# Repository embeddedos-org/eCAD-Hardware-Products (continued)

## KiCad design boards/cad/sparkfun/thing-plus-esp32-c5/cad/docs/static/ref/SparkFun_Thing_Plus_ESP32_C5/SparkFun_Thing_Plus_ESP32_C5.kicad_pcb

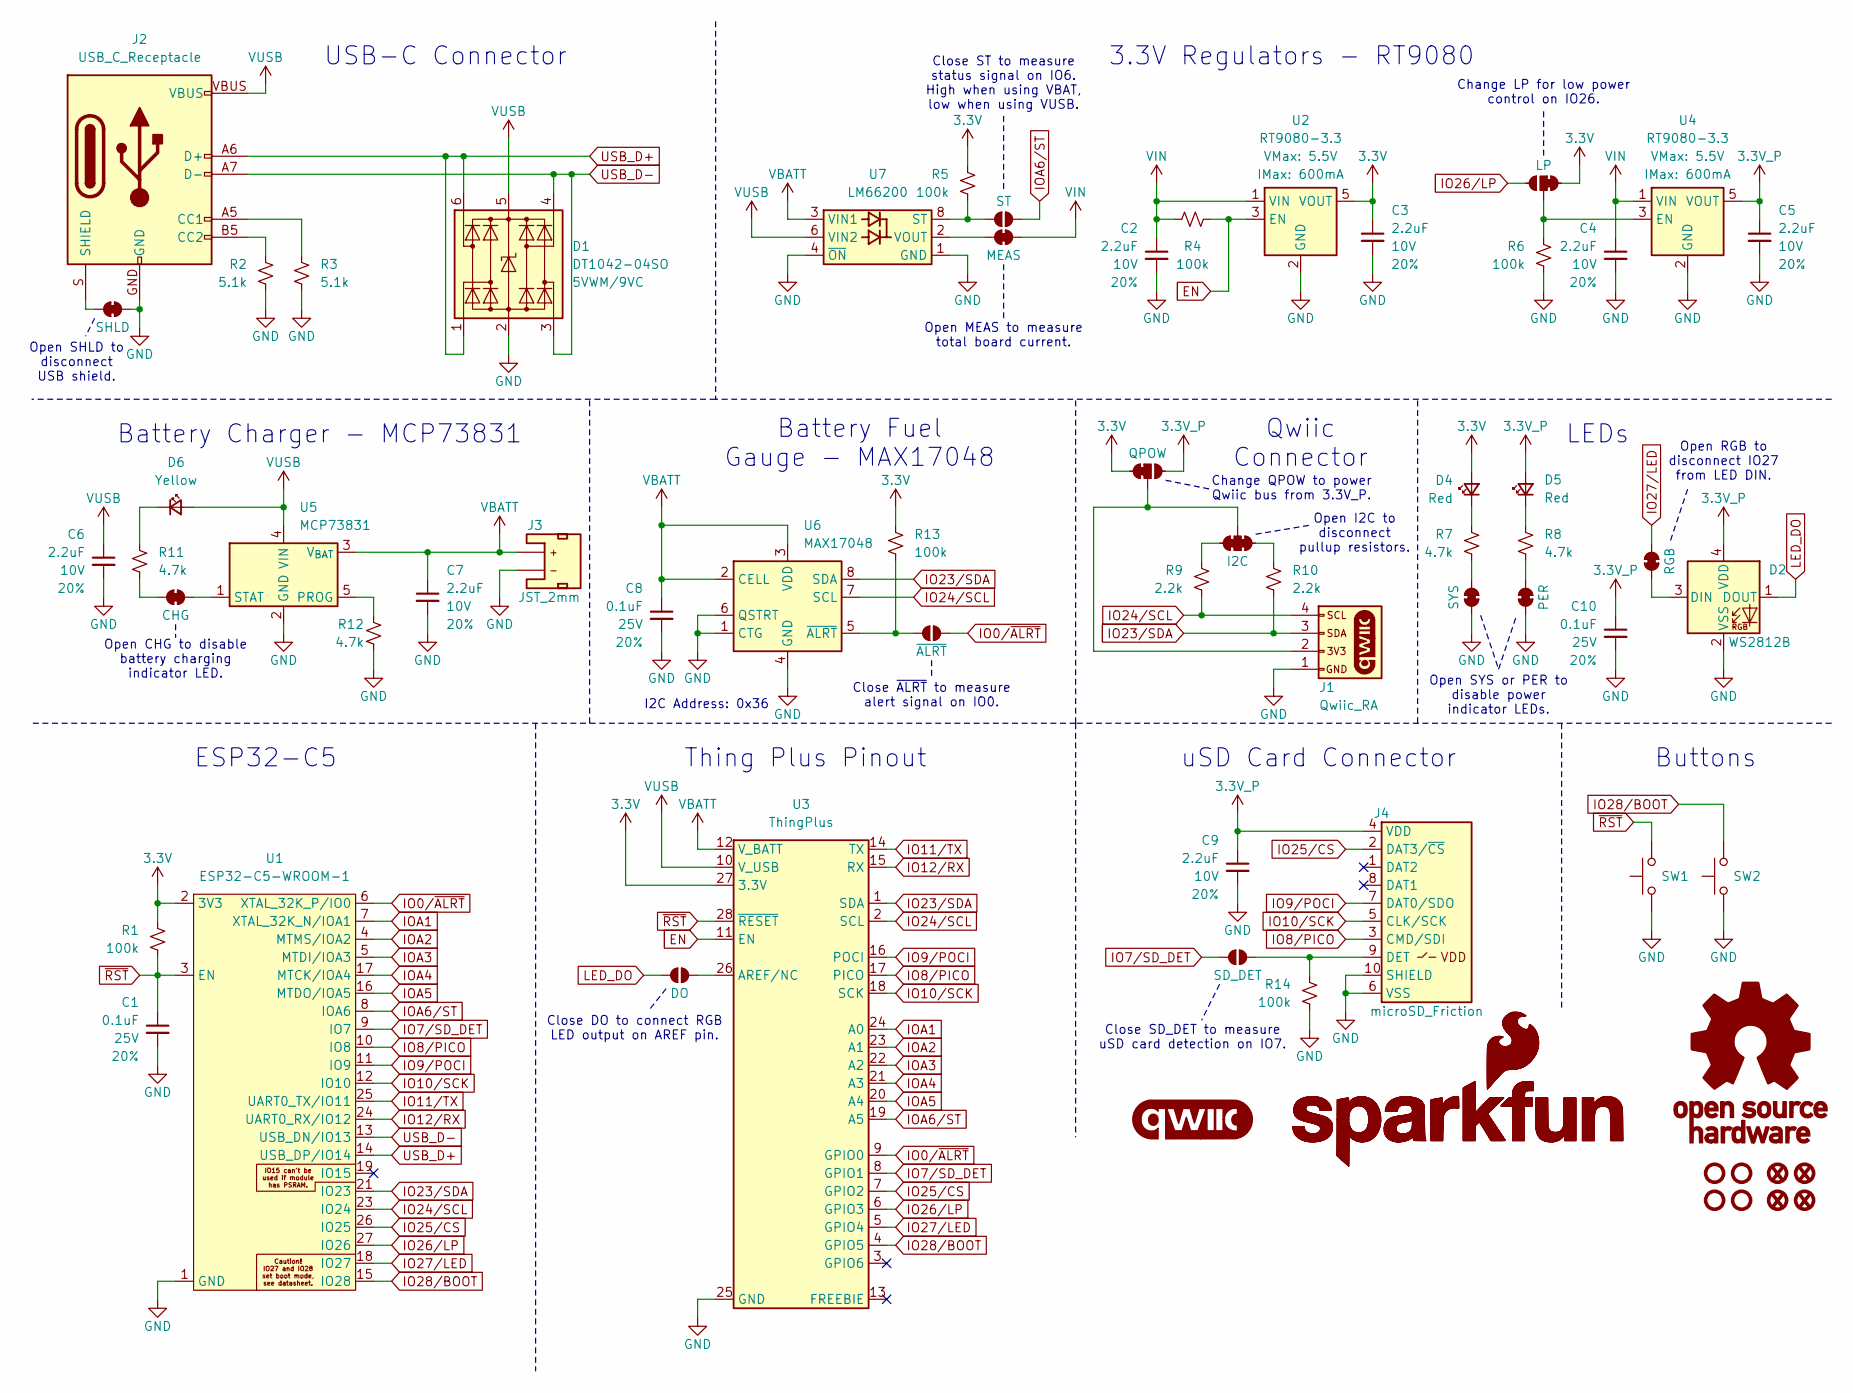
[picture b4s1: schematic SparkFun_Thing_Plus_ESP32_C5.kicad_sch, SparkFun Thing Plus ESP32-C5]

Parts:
C1, C8, C10: 0.1uF; C_0603_1608Metric; Voltage 25V; Tolerance 20%
C2, C3, C4, C5, C6, C7, C9: 2.2uF; C_0603_1608Metric; Voltage 10V; Tolerance 20%
D1: DT1042-04SO; SOT23-6; Rating 5VWM/9VC
D2: WS2812B; WS2812_2020
D4, D5: Red; LED_0603_1608Metric_Red
D6: Yellow; LED_0603_1608Metric_Yellow
FID1, FID2, FID3, FID4: Fiducial_0.5mm; Fiducial_0.5mm_Mask1mm
G1: SparkFun_Logo; SparkFun_Logo_8mm
G2: SparkFun_Logo
G3: OSHW_Logo; Creative_Commons_License
G4: qwiic_Logo
J1: Qwiic_RA; JST_1x04_P1.0mm_Horizontal_SMD
J2: USB_C_Receptacle; USB-C_16
J3: JST_2mm; JST_1x02_P2.0mm_Horizontal_SMD
J4: microSD_Friction; microSD_Friction_Fit_Common
JP1: SHLD; Jumper_2_NC_Trace
JP2: MEAS; Jumper_2_PTH_SMD_Combo-NC
JP3: LP; Jumper_3_NC-1_Trace
JP4: SYS; Jumper_2_NC_Trace
JP5: PER; Jumper_2_NC_Trace
JP6: I2C; Jumper_3_NC-2_Trace
JP7: QPOW; Jumper_3_NC-1_Trace
JP8: CHG; Jumper_2_NC_Trace
JP9: ~{ALRT}; Jumper_2_NO
JP10: SD_DET; Jumper_2_NO
JP11: DO; Jumper_2_NO
JP12: RGB; Jumper_2_NC_Trace
JP13: ST; Jumper_2_NO
R1, R4, R5, R6, R13, R14: 100k; R_0603_1608Metric
R2, R3: 5.1k; R_0603_1608Metric
R7, R8, R11, R12: 4.7k; R_0603_1608Metric
R9, R10: 2.2k; R_0603_1608Metric
ST1, ST2, ST3, ST4: Stand_off; Standoff
SW1, SW2: SMD_4.6x2.8mm_h2.5mm; Push_SMD_4.6x2.8mm_h2.5mm
U1: ESP32-C5-WROOM-1; ESP32-C5-WROOM-1-NARROW
U2, U4: RT9080-3.3; SOT23-5
U3: ThingPlus; ThingPlus_With_Connectors
U5: MCP73831; SOT23-5
U6: MAX17048; DFN-8_2x2mm_P0.5mm_EP1.2x0.8mm
U7: LM66200; SOT-583-8

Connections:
3.3V: C3.1, D4.2 (A), JP3.1 (A), JP7.1 (A), R1.2, R5.2, R13.2, U1.2 (3V3), U2.5 (VOUT), U3.27 (3.3V)
3.3V_P: C5.1, C9.1, C10.1, D2.4 (VDD), D5.2 (A), J4.4 (VDD), JP7.3 (C), U4.5 (VOUT)
EN: R4.2, U2.3 (EN), U3.11 (EN)
GND: C1.2, C2.2, C3.2, C4.2, C5.2, C6.2, C7.2, C8.2, C9.2, C10.2, D1.2 (GND), D2.2 (VSS), J1.1, J2.GND, J3.1 (-), J4.6 (VSS), J4.10 (SHIELD), JP1.2 (B), JP4.1 (A), JP5.1 (A), R2.1, R3.1, R6.1, R12.1, R14.1, SW1.1, SW2.1, U1.1 (GND), U1.28 (GND), U1.EPAD (GND), U2.2 (GND), U3.25 (GND), U4.2 (GND), U5.2 (GND), U6.1 (CTG), U6.4 (GND), U6.6 (QSTRT), U6.9 (GND), U7.1 (GND), U7.4 (~ON), U7.5 (GND)
IO0/~ALRT: JP9.2 (B), U1.6 (XTAL_32K_P/IO0), U3.9 (GPIO0)
IO7/SD_DET: JP10.1 (A), U1.9 (IO7), U3.8 (GPIO1)
IO8/PICO: J4.3 (CMD/SDI), U1.10 (IO8), U3.17 (PICO)
IO9/POCI: J4.7 (DAT0/SDO), U1.11 (IO9), U3.16 (POCI)
IO10/SCK: J4.5 (CLK/SCK), U1.12 (IO10), U3.18 (SCK)
IO11/TX: U1.25 (UART0_TX/IO11), U3.14 (TX)
IO12/RX: U1.24 (UART0_RX/IO12), U3.15 (RX)
IO23/SDA: J1.3, R10.1, U1.21 (IO23), U3.1 (SDA), U6.8 (SDA)
IO24/SCL: J1.4, R9.1, U1.23 (IO24), U3.2 (SCL), U6.7 (SCL)
IO25/CS: J4.2 (DAT3/~CS), U1.26 (IO25), U3.7 (GPIO2)
IO26/LP: JP3.3 (C), U1.27 (IO26), U3.6 (GPIO3)
IO27/LED: JP12.2 (B), U1.18 (IO27), U3.5 (GPIO4)
IO28/BOOT: SW2.2, U1.15 (IO28), U3.4 (GPIO5)
IOA1: U1.7 (XTAL_32K_N/IOA1), U3.24 (A0)
IOA2: U1.4 (MTMS/IOA2), U3.23 (A1)
IOA3: U1.5 (MTDI/IOA3), U3.22 (A2)
IOA4: U1.17 (MTCK/IOA4), U3.21 (A3)
IOA5: U1.16 (MTDO/IOA5), U3.20 (A4)
IOA6/ST: JP13.2 (B), U1.8 (IOA6), U3.19 (A5)
LED_DO: D2.1 (DOUT), JP11.1 (A)
unnamed: D2.3 (DIN), JP12.1 (A)
unnamed: D4.1 (K), R7.2
unnamed: D5.1 (K), R8.2
unnamed: D6.1 (K), R11.2
unnamed: J1.2, JP6.2 (B), JP7.2 (B)
unnamed: J2.A5 (CC1), R3.2
unnamed: J2.B5 (CC2), R2.2
unnamed: J2.S (SHIELD), JP1.1 (A)
unnamed: J4.9 (DET), JP10.2 (B), R14.2
unnamed: JP2.1 (A), U7.2 (VOUT), U7.7 (VOUT)
unnamed: JP3.2 (B), R6.2, U4.3 (EN)
unnamed: JP4.2 (B), R7.1
unnamed: JP5.2 (B), R8.1
unnamed: JP6.1 (A), R10.2
unnamed: JP6.3 (C), R9.2
unnamed: JP8.1 (A), R11.1
unnamed: JP8.2 (B), U5.1 (STAT)
unnamed: JP9.1 (A), R13.1, U6.5 (~ALRT)
unnamed: JP11.2 (B), U3.26 (AREF/NC)
unnamed: JP13.1 (A), R5.1, U7.8 (ST)
unnamed: R12.2, U5.5 (PROG)
USB_D+: D1.1 (I/O1), D1.6 (I/O4), J2.A6 (D+), J2.B6 (D+), U1.14 (USB_DP/IO14)
USB_D-: D1.3 (I/O2), D1.4 (I/O3), J2.A7 (D-), J2.B7 (D-), U1.13 (USB_DN/IO13)
VBATT: C7.1, C8.1, J3.2 (+), U3.12 (V_BATT), U5.3 (V_{BAT}), U6.2 (CELL), U6.3 (VDD), U7.3 (VIN1)
VIN: C2.1, C4.1, JP2.2 (B), R4.1, U2.1 (VIN), U4.1 (VIN)
VUSB: C6.1, D1.5 (VCC), D6.2 (A), J2.VBUS, U3.10 (V_USB), U5.4 (VIN), U7.6 (VIN2)
~RST: C1.1, R1.1, SW1.2, U1.3 (EN), U3.28 (~RESET)

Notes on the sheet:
uSD Card Connector
Open MEAS to measure total board current.
Close SD_DET to measure uSD card detection on IO7.
Open RGB to disconnect IO27 from LED DIN.
3.3V Regulators - RT9080
Close DO to connect RGB LED output on AREF pin.
Qwiic Connector
Thing Plus Pinout
Battery Fuel Gauge - MAX17048
Open SYS or PER to disable power indicator LEDs.
ESP32-C5
Change LP for low power control on IO26.
Close ~{ALRT} to measure alert signal on IO0.
LEDs
Open SHLD to disconnect USB shield.
I2C Address: 0x36
Open CHG to disable battery charging indicator LED.
Battery Charger - MCP73831
Close ST to measure status signal on IO6. High when using VBAT, low when using VUSB.
Open I2C to disconnect pullup resistors.
Change QPOW to power Qwiic bus from 3.3V_P.
USB-C Connector
Buttons

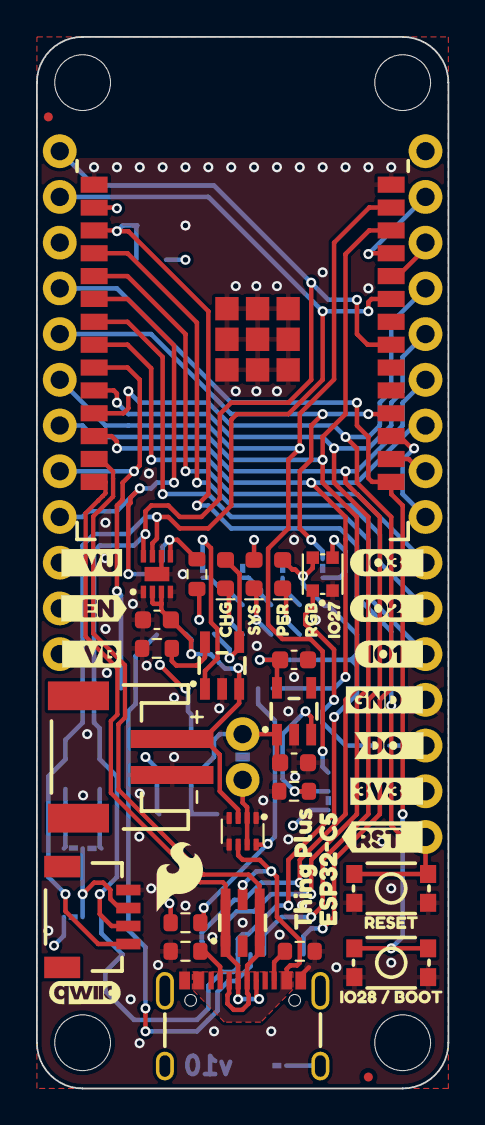
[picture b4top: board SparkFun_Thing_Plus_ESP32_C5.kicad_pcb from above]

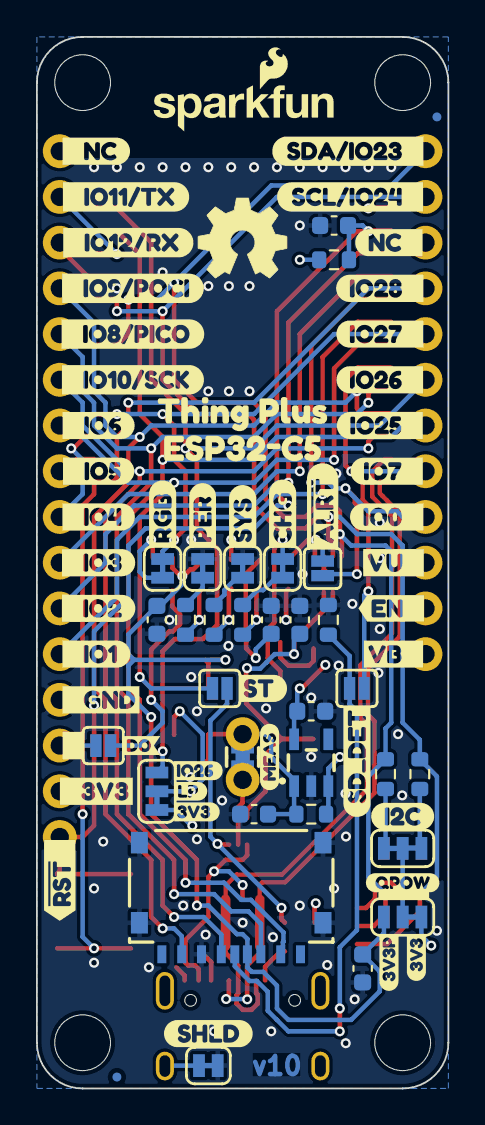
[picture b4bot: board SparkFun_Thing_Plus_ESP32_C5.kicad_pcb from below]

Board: 4 copper layers, 22.9 x 58.4 mm, 130 parts (79 on the bottom side), 51 nets.

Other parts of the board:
Ref**: Val**; OSHW_Logo_5mm
kibuzzard-695FE9C9: G***; kibuzzard-695FE9C9
kibuzzard-695FE9D0: G***; kibuzzard-695FE9D0
kibuzzard-695FE9E2: G***; kibuzzard-695FE9E2
kibuzzard-695FE9F2: G***; kibuzzard-695FE9F2
kibuzzard-695FEA02: G***; kibuzzard-695FEA02
kibuzzard-695FEA05: G***; kibuzzard-695FEA05
kibuzzard-695FEA11: G***; kibuzzard-695FEA11
kibuzzard-695FEF26: G***; kibuzzard-695FEF26
kibuzzard-695FEF91: G***; kibuzzard-695FEF91
kibuzzard-695FF00A: G***; kibuzzard-695FF00A
kibuzzard-695FF0A1: G***; kibuzzard-695FF0A1
kibuzzard-695FF0A5: G***; kibuzzard-695FF0A5
kibuzzard-695FF0AF: G***; kibuzzard-695FF0AF
kibuzzard-695FF0B3: G***; kibuzzard-695FF0B3
kibuzzard-695FF0B8: G***; kibuzzard-695FF0B8
kibuzzard-695FF0BC: G***; kibuzzard-695FF0BC
kibuzzard-695FF0C2: G***; kibuzzard-695FF0C2
kibuzzard-695FF0C6: G***; kibuzzard-695FF0C6
kibuzzard-695FF03A: G***; kibuzzard-695FF03A
kibuzzard-695FF06A: G***; kibuzzard-695FF06A
kibuzzard-695FF07F: G***; kibuzzard-695FF07F
kibuzzard-695FF09A: G***; kibuzzard-695FF09A
kibuzzard-695FF023: G***; kibuzzard-695FF023
kibuzzard-695FF029: G***; kibuzzard-695FF029
kibuzzard-695FF31A: G***; kibuzzard-695FF31A
kibuzzard-695FF032: G***; kibuzzard-695FF032
kibuzzard-695FF036: G***; kibuzzard-695FF036
kibuzzard-695FF063: G***; kibuzzard-695FF063
kibuzzard-695FF074: G***; kibuzzard-695FF074
kibuzzard-695FF079: G***; kibuzzard-695FF079
kibuzzard-695FF661: G***; kibuzzard-695FF661
kibuzzard-695FF668: G***; kibuzzard-695FF668
kibuzzard-695FF676: G***; kibuzzard-695FF676
kibuzzard-6966A94A: G***; kibuzzard-6966A94A
kibuzzard-6966B7BA: G***; kibuzzard-6966B7BA
kibuzzard-6966B7FC: G***; kibuzzard-6966B7FC
kibuzzard-6966B682: G***; kibuzzard-6966B682
kibuzzard-6966B814: G***; kibuzzard-6966B814
kibuzzard-6966CACE: G***; kibuzzard-6966CACE
kibuzzard-6966CF2A: G***; kibuzzard-6966CF2A
kibuzzard-6966CFDE: G***; kibuzzard-6966CFDE
kibuzzard-6966D2E6: G***; kibuzzard-6966D2E6
kibuzzard-6966D2EC: G***; kibuzzard-6966D2EC
kibuzzard-6966D4C9: G***; kibuzzard-6966D4C9
kibuzzard-69602AEE: G***; kibuzzard-69602AEE
kibuzzard-69602AF5: G***; kibuzzard-69602AF5
kibuzzard-69602C96: G***; kibuzzard-69602C96
kibuzzard-69602E66: G***; kibuzzard-69602E66
kibuzzard-69602E70: G***; kibuzzard-69602E70
kibuzzard-69603B5F: G***; kibuzzard-69603B5F
kibuzzard-69603FA6: G***; kibuzzard-69603FA6
kibuzzard-69603FF7: G***; kibuzzard-69603FF7
kibuzzard-69604BB0: G***; kibuzzard-69604BB0
kibuzzard-69604BBF: G***; kibuzzard-69604BBF
kibuzzard-69618FC6: G***; kibuzzard-69618FC6
kibuzzard-696024A3: G***; kibuzzard-696024A3
kibuzzard-696024E0: G***; kibuzzard-696024E0
kibuzzard-696040AD: G***; kibuzzard-696040AD
kibuzzard-696044C8: G***; kibuzzard-696044C8
kibuzzard-696044CC: G***; kibuzzard-696044CC
kibuzzard-6960344B: G***; kibuzzard-6960344B
kibuzzard-6960530A: G***; kibuzzard-6960530A
kibuzzard-69602539: G***; kibuzzard-69602539
kibuzzard-69605303: G***; kibuzzard-69605303
kibuzzard-69727252: G***; kibuzzard-69727252

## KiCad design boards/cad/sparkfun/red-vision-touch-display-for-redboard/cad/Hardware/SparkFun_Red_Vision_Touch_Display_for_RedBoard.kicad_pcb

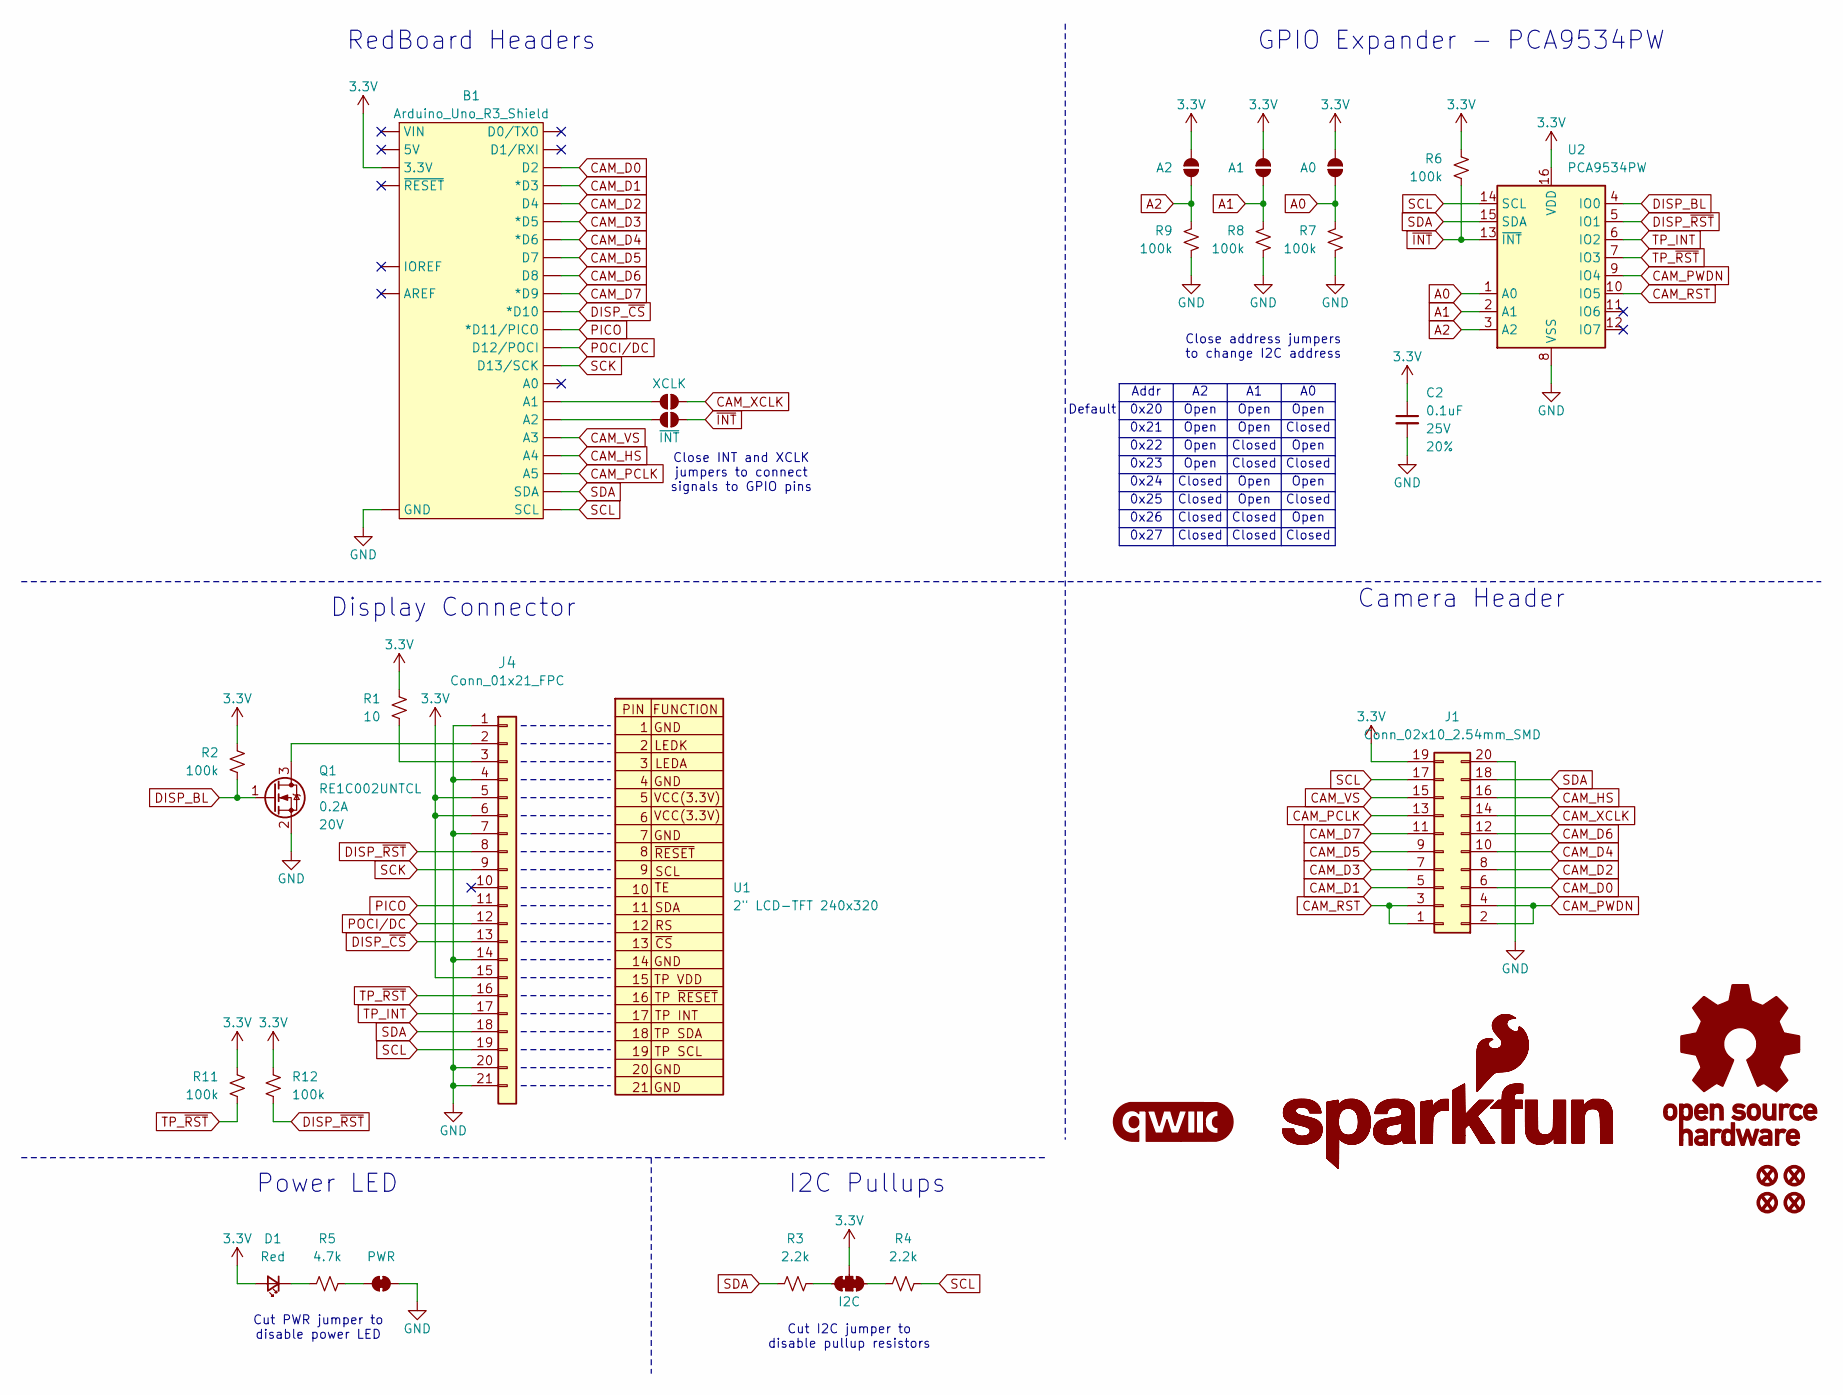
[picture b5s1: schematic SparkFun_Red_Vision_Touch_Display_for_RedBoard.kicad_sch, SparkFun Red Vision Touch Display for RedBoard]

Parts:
B1: Arduino_Uno_R3_Shield; Uno_R3_Shield_NoLabels
C2: 0.1uF; C_0603_1608Metric; Voltage 25V; Tolerance 20%
D1: Red; LED_0603_1608Metric_Red
FID1, FID2, FID3, FID4: Fiducial_0.5mm; Fiducial_0.5mm_Mask1mm
G1: SparkFun_Logo; SparkFun_Logo_8mm
G2: SparkFun_Logo
G3: OSHW_Logo; Creative_Commons_License
G4: qwiic_Logo
J1: Conn_02x10_2.54mm_SMD; 2x10_P2.54mm_Socket_Vertical_SMD
J4: Conn_01x21_FPC; FPC_1x21_P0.3mm_Horizontal_DualContact
JP1: I2C; Jumper_3_NC-2_Trace
JP13: XCLK; Jumper_2_NO
JP14: A0; Jumper_2_NO
JP15: A1; Jumper_2_NO
JP16: A2; Jumper_2_NO
JP21: PWR; Jumper_2_NC_Trace
JP22: ~{INT}; Jumper_2_NO
Q1: RE1C002UNTCL; SC-89 SOT-490
R1: 10; R_0603_1608Metric
R2, R6, R7, R8, R9, R11, R12: 100k; R_0603_1608Metric
R3, R4: 2.2k; R_0603_1608Metric
R5: 4.7k; R_0603_1608Metric
U1: 2" LCD-TFT 240x320; LCD_TFT_2.0in_Waveshare_Outline
U2: PCA9534PW; TSSOP-16_4.4x5mm_P0.65mm

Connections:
3.3V: B1.3.3V, C2.1, D1.2 (A), J1.19, J4.5, J4.6, J4.15, JP1.2 (B), JP14.2 (B), JP15.2 (B), JP16.2 (B), R1.2, R2.2, R6.2, R11.2, R12.2, U2.16 (VDD)
A0: JP14.1 (A), R7.2, U2.1 (A0)
A1: JP15.1 (A), R8.2, U2.2 (A1)
A2: JP16.1 (A), R9.2, U2.3 (A2)
CAM_D0: B1.D2, J1.6
CAM_D1: B1.D3 (*D3), J1.5
CAM_D2: B1.D4, J1.8
CAM_D3: B1.D5 (*D5), J1.7
CAM_D4: B1.D6 (*D6), J1.10
CAM_D5: B1.D7, J1.9
CAM_D6: B1.D8, J1.12
CAM_D7: B1.D9 (*D9), J1.11
CAM_HS: B1.A4, J1.16
CAM_PCLK: B1.A5, J1.13
CAM_PWDN: J1.2, J1.4, U2.9 (IO4)
CAM_RST: J1.1, J1.3, U2.10 (IO5)
CAM_VS: B1.A3, J1.15
CAM_XCLK: J1.14, JP13.1 (A)
DISP_BL: Q1.1 (G), R2.1, U2.4 (IO0)
DISP_~CS: B1.D10 (*D10), J4.13
DISP_~RST: J4.8, R12.1, U2.5 (IO1)
GND: B1.GND, C2.2, J1.20, J4.1, J4.4, J4.7, J4.14, J4.20, J4.21, JP21.2 (B), Q1.2 (S), R7.1, R8.1, R9.1, U2.8 (VSS)
unnamed: D1.1 (K), R5.2
unnamed: J4.2, Q1.3 (D)
unnamed: J4.3, R1.1
unnamed: JP1.1 (A), R4.1
unnamed: JP1.3 (C), R3.2
unnamed: B1.A1, JP13.2 (B)
unnamed: JP21.1 (A), R5.1
unnamed: B1.A2, JP22.2 (B)
PICO: B1.D11 (*D11/PICO), J4.11
POCI/DC: B1.D12 (D12/POCI), J4.12
SCK: B1.D13 (D13/SCK), J4.9
SCL: B1.SCL, J1.17, J4.19, R4.2, U2.14 (SCL)
SDA: B1.SDA, J1.18, J4.18, R3.1, U2.15 (SDA)
TP_INT: J4.17, U2.6 (IO2)
TP_~RST: J4.16, R11.1, U2.7 (IO3)
~INT: JP22.1 (A), R6.1, U2.13 (~INT)

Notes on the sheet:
Open
0x20
Closed
Cut PWR jumper to disable power LED
0x22
0x27
0x24
GPIO Expander - PCA9534PW
Close address jumpers to change I2C address
Default
Addr
Cut I2C jumper to disable pullup resistors
RedBoard Headers
Camera Header
Close INT and XCLK jumpers to connect signals to GPIO pins
0x26
0x23
Display Connector
0x21
0x25
Power LED
I2C Pullups

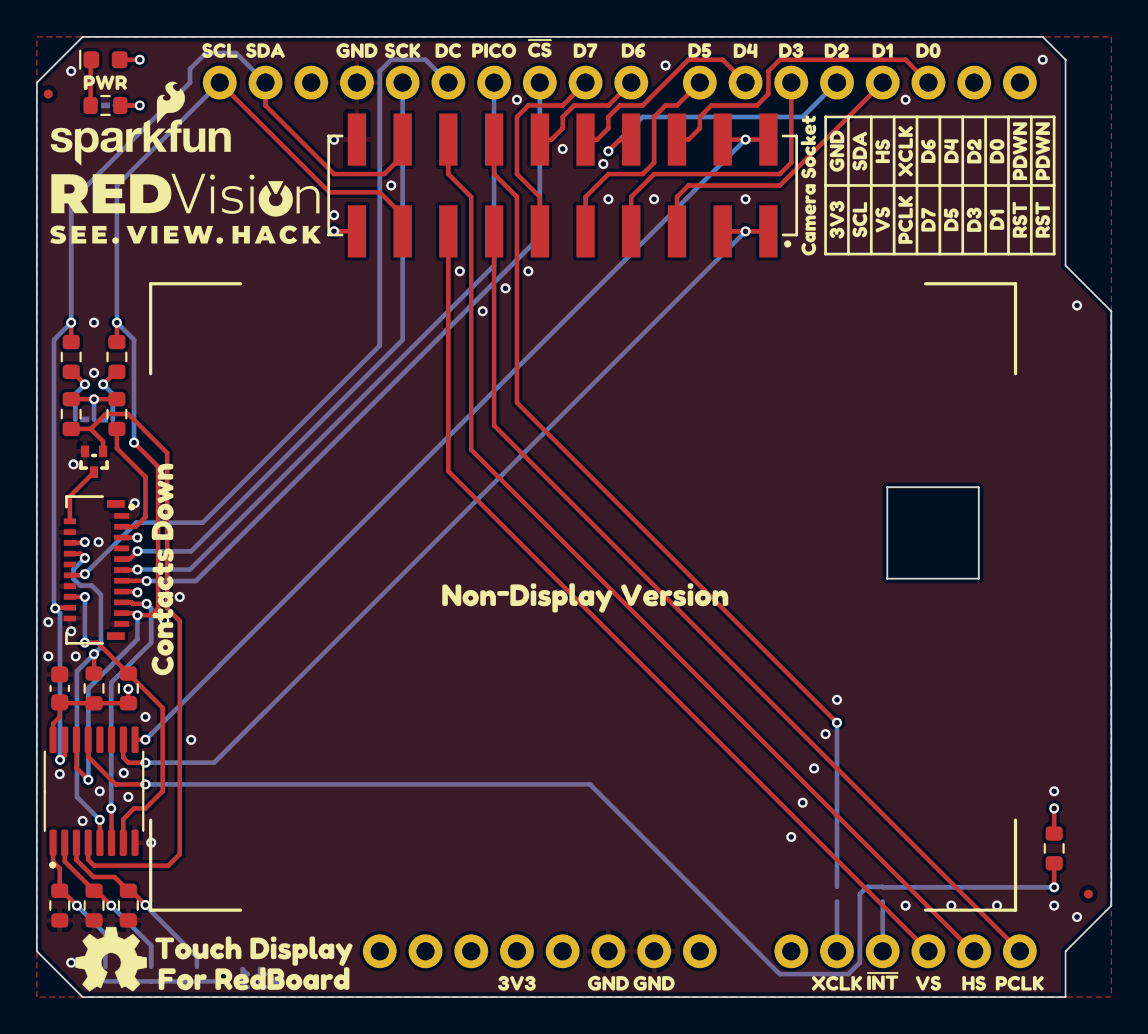
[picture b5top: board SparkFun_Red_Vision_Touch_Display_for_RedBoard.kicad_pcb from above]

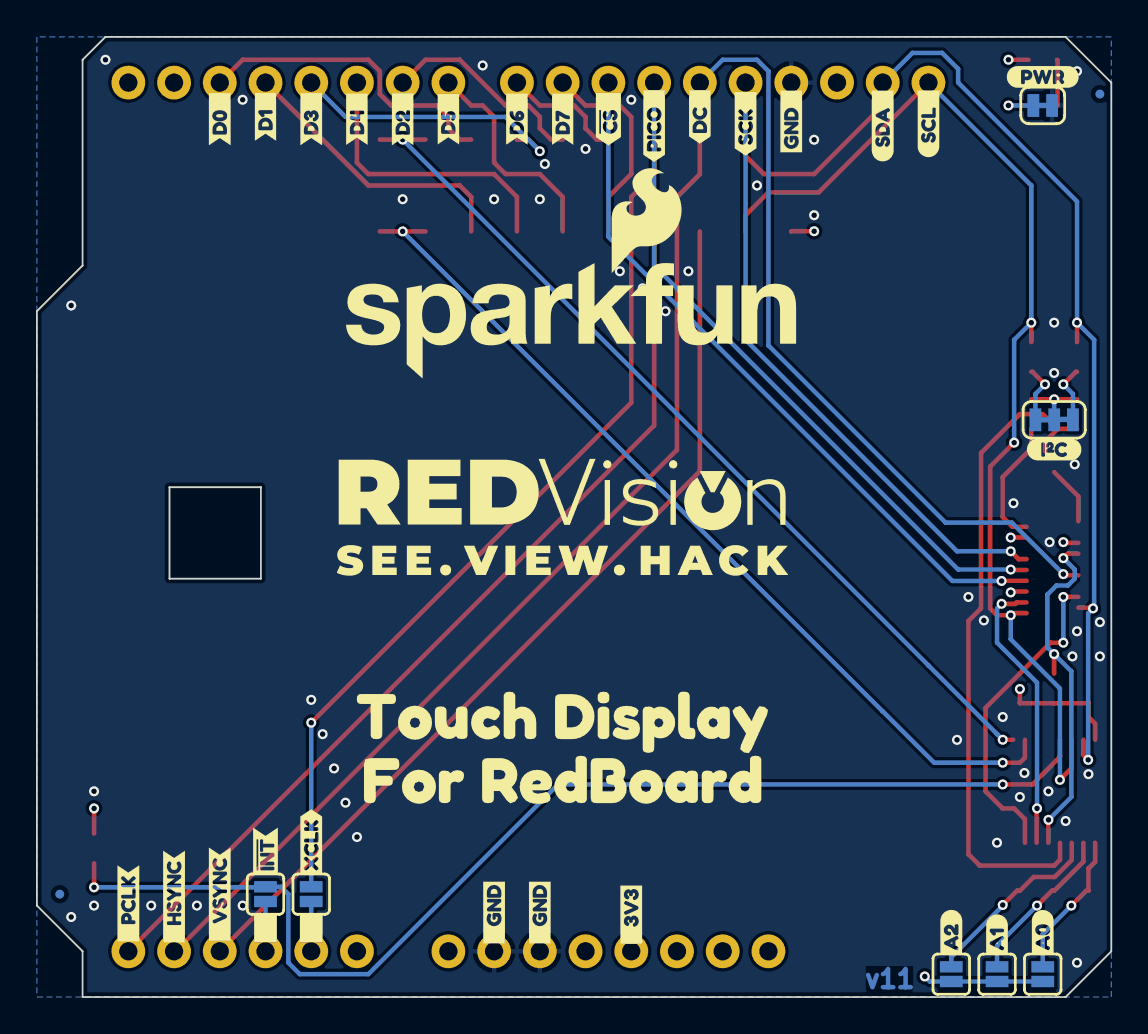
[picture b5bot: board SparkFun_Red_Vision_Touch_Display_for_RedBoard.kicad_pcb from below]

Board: 4 copper layers, 59.7 x 53.3 mm, 111 parts (39 on the bottom side), 38 nets.

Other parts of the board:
Ref**: Val**; OSHW_Logo_4mm
kibuzzard-67A69C5F, kibuzzard-67A69C5F#2: G***; kibuzzard-67A69C5F
kibuzzard-67A69CD2, kibuzzard-67A69CD2#2: G***; kibuzzard-67A69CD2
kibuzzard-67A69CDC: G***; kibuzzard-67A69CDC
kibuzzard-67A69CE2: G***; kibuzzard-67A69CE2
kibuzzard-67A69CE6: G***; kibuzzard-67A69CE6
kibuzzard-67A69CEA: G***; kibuzzard-67A69CEA
kibuzzard-67A69CFF: G***; kibuzzard-67A69CFF
kibuzzard-67A69D0C: G***; kibuzzard-67A69D0C
kibuzzard-67A69D0F: G***; kibuzzard-67A69D0F
kibuzzard-67A69D1B: G***; kibuzzard-67A69D1B
kibuzzard-67A69D2C: G***; kibuzzard-67A69D2C
kibuzzard-67A69D2F: G***; kibuzzard-67A69D2F
kibuzzard-67A69D05: G***; kibuzzard-67A69D05
kibuzzard-67A69D16: G***; kibuzzard-67A69D16
kibuzzard-67A69D28: G***; kibuzzard-67A69D28
kibuzzard-67A69D32: G***; kibuzzard-67A69D32
kibuzzard-67A69E51: G***; kibuzzard-67A69E51
kibuzzard-67A69E55: G***; kibuzzard-67A69E55
kibuzzard-67B3FFE0: G***; kibuzzard-67B3FFE0
kibuzzard-67C124A5: G***; kibuzzard-67C124A5
kibuzzard-67C1248C: G***; kibuzzard-67C1248C
kibuzzard-68B0C822: G***; kibuzzard-68B0C822
kibuzzard-68B0C855: G***; kibuzzard-68B0C855
kibuzzard-68B1DD36: G***; kibuzzard-68B1DD36
kibuzzard-68B9B772: G***; kibuzzard-68B9B772
kibuzzard-68B9BC57: G***; kibuzzard-68B9BC57
kibuzzard-68B9BC59: G***; kibuzzard-68B9BC59
kibuzzard-68B9BC63: G***; kibuzzard-68B9BC63
kibuzzard-68B9BCE4: G***; kibuzzard-68B9BCE4
kibuzzard-68B9BCEA: G***; kibuzzard-68B9BCEA
kibuzzard-68B9BCF4: G***; kibuzzard-68B9BCF4
kibuzzard-68B9BD3D: G***; kibuzzard-68B9BD3D
kibuzzard-68B9BD4B: G***; kibuzzard-68B9BD4B
kibuzzard-68B9BD7F: G***; kibuzzard-68B9BD7F
kibuzzard-68B9BD9B: G***; kibuzzard-68B9BD9B
kibuzzard-68B9BD55: G***; kibuzzard-68B9BD55
kibuzzard-68B9BD76: G***; kibuzzard-68B9BD76
kibuzzard-68B9BDA0: G***; kibuzzard-68B9BDA0
kibuzzard-68B9BDA7: G***; kibuzzard-68B9BDA7
kibuzzard-68B9BDC0: G***; kibuzzard-68B9BDC0
kibuzzard-68B9BDC6: G***; kibuzzard-68B9BDC6
kibuzzard-68B9BDCB: G***; kibuzzard-68B9BDCB
kibuzzard-68B9BE6E: G***; kibuzzard-68B9BE6E
kibuzzard-68B9BE9E: G***; kibuzzard-68B9BE9E
kibuzzard-68B9BE85: G***; kibuzzard-68B9BE85
kibuzzard-68B9BE89: G***; kibuzzard-68B9BE89
kibuzzard-68B9BEAF: G***; kibuzzard-68B9BEAF
kibuzzard-68B9BECE, kibuzzard-68B9BECE#2: G***; kibuzzard-68B9BECE
kibuzzard-68B9BED6: G***; kibuzzard-68B9BED6
kibuzzard-68B9BEDF: G***; kibuzzard-68B9BEDF
kibuzzard-68B9BEFF: G***; kibuzzard-68B9BEFF
kibuzzard-68B9BF01: G***; kibuzzard-68B9BF01
kibuzzard-68B9BF2B: G***; kibuzzard-68B9BF2B
kibuzzard-68B9BF3C: G***; kibuzzard-68B9BF3C
kibuzzard-68B9BF4D: G***; kibuzzard-68B9BF4D
kibuzzard-68B9BF5D: G***; kibuzzard-68B9BF5D
kibuzzard-68B9BF06: G***; kibuzzard-68B9BF06
kibuzzard-68B9BF8B: G***; kibuzzard-68B9BF8B
kibuzzard-68B9BF11: G***; kibuzzard-68B9BF11
kibuzzard-68B9BF14: G***; kibuzzard-68B9BF14
kibuzzard-68B9BF19: G***; kibuzzard-68B9BF19
kibuzzard-68B9BF49: G***; kibuzzard-68B9BF49
kibuzzard-68B9BF52: G***; kibuzzard-68B9BF52
kibuzzard-68B9BF61: G***; kibuzzard-68B9BF61
kibuzzard-68B9BF65: G***; kibuzzard-68B9BF65
kibuzzard-68B9BF69: G***; kibuzzard-68B9BF69
kibuzzard-68B202D3: G***; kibuzzard-68B202D3
kibuzzard-68B202D8: G***; kibuzzard-68B202D8
kibuzzard-68EEA4F5: G***; kibuzzard-68EEA4F5
kibuzzard-68EEA4FB: G***; kibuzzard-68EEA4FB
kibuzzard-68EEA50D: G***; kibuzzard-68EEA50D
kibuzzard-68EEA51B: G***; kibuzzard-68EEA51B
kibuzzard-68EEA508: G***; kibuzzard-68EEA508
kibuzzard-68EEA511: G***; kibuzzard-68EEA511
kibuzzard-68EEA516: G***; kibuzzard-68EEA516
kibuzzard-68EEA520: G***; kibuzzard-68EEA520
